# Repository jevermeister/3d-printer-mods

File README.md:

# 3d-printer-mods
my 3d printer mods which might or might not be useful

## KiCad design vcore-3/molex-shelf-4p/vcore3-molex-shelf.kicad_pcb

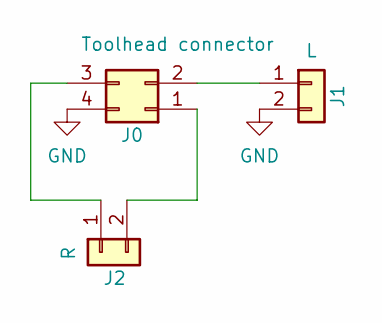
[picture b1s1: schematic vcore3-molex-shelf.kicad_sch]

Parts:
J0: Toolhead connector; Molex_Micro-Fit_3.0_43045-0412_2x02_P3.00mm_Vertical
J1: L; CONN-TH_2P-P5.08_796949-2
J2: R; CONN-TH_2P-P5.08_796949-2

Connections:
GND: J0.4, J1.2
unnamed: J0.1, J2.2
unnamed: J0.2, J1.1
unnamed: J0.3, J2.1

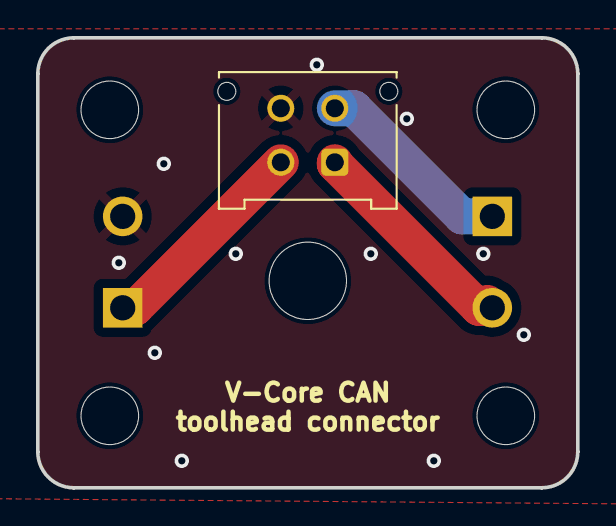
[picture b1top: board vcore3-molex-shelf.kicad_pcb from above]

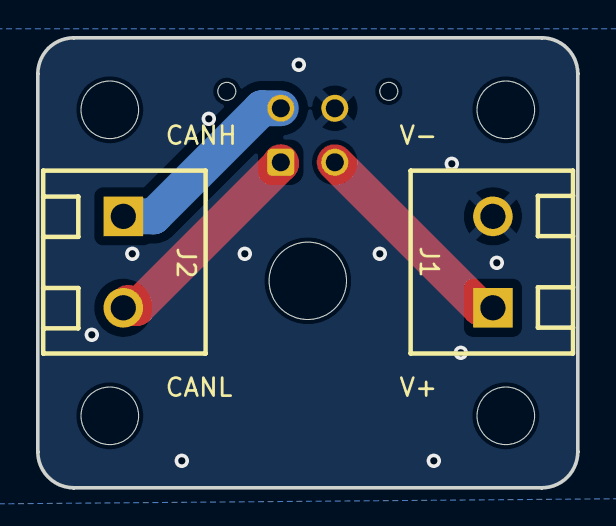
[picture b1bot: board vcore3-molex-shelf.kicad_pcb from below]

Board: 2 copper layers, 30.0 x 25.0 mm, 3 parts (2 on the bottom side), 4 nets.

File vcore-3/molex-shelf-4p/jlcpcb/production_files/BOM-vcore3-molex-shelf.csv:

Comment,Designator,Footprint,LCSC,Quantity
Toolhead connector,J0,Molex_Micro-Fit_3.0_43045-0412_2x02_P3.00mm_Vertical,,1
R,J2,CONN-TH_2P-P5.08_796949-2,,1
L,J1,CONN-TH_2P-P5.08_796949-2,,1

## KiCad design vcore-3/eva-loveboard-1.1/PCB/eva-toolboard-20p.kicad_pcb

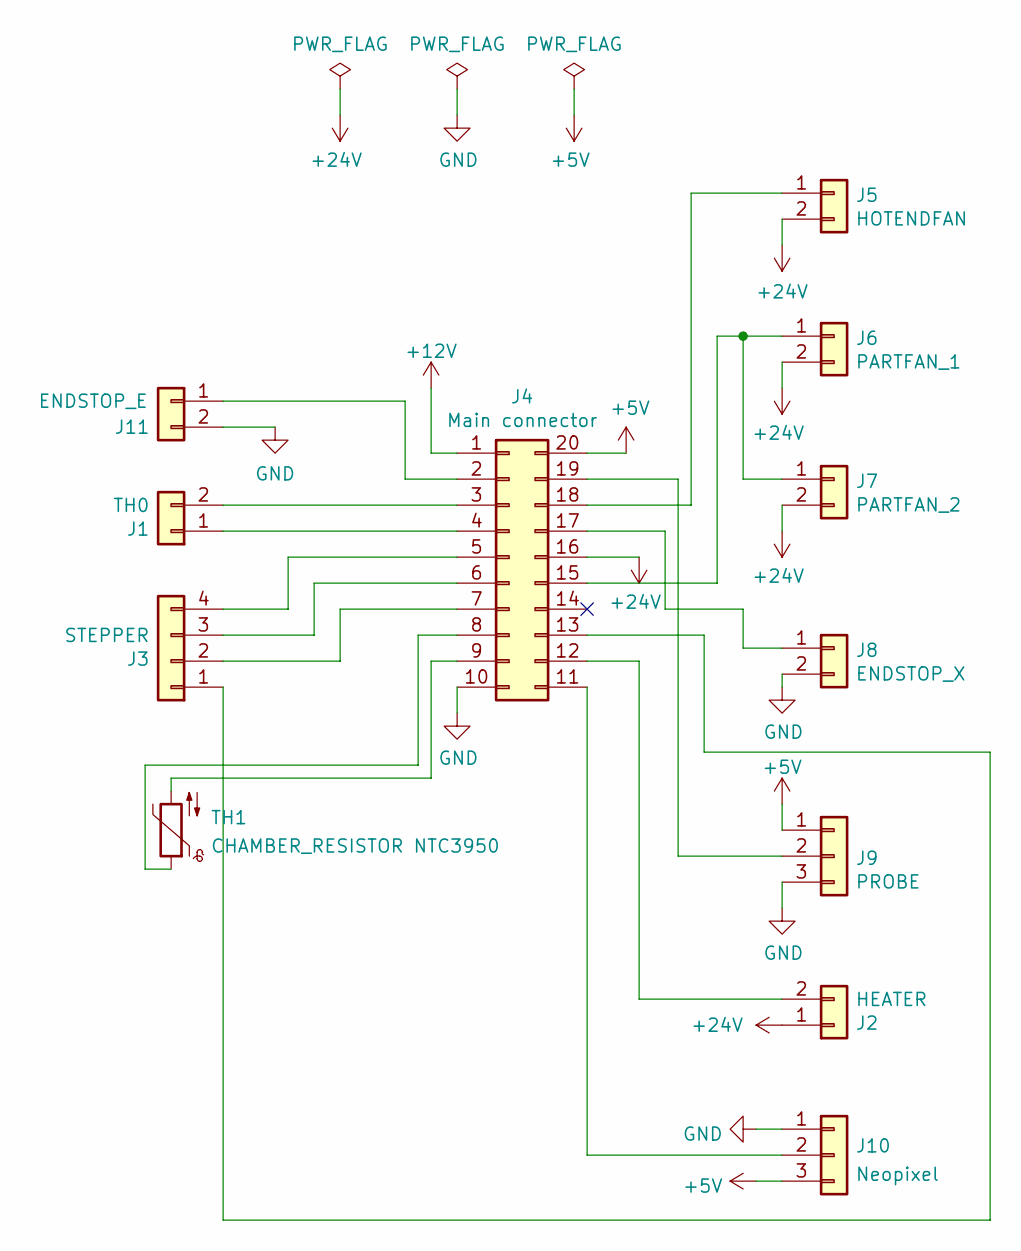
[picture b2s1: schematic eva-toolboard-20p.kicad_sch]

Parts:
J1: TH0; JST_PH_B2B-PH-K_1x02_P2.00mm_Vertical
J2: HEATER; Molex_Micro-Fit_3.0_43650-0200_1x02_P3.00mm_Horizontal
J3: STEPPER; JST_PH_B4B-PH-K_1x04_P2.00mm_Vertical
J4: Main connector; Molex_Micro-Fit_3.0_43045-2000_2x10_P3.00mm_Horizontal
J5: HOTENDFAN; JST_PH_S2B-PH-K_1x02_P2.00mm_Horizontal
J6: PARTFAN_1; JST_PH_S2B-PH-K_1x02_P2.00mm_Horizontal
J7: PARTFAN_2; JST_PH_B2B-PH-K_1x02_P2.00mm_Vertical
J8: ENDSTOP_X; JST_PH_S2B-PH-K_1x02_P2.00mm_Horizontal
J9: PROBE; JST_PH_S3B-PH-K_1x03_P2.00mm_Horizontal
J10: Neopixel; JST_PH_S3B-PH-K_1x03_P2.00mm_Horizontal
J11: ENDSTOP_E; JST_PH_B2B-PH-K_1x02_P2.00mm_Vertical
TH1: CHAMBER_RESISTOR NTC3950; D_A-405_P7.62mm_Horizontal

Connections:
+5V: J4.20, J9.1, J10.3
+12V: J4.1
+24V: J2.1, J4.16, J5.2, J6.2, J7.2
GND: J4.10, J8.2, J9.3, J10.1, J11.2
unnamed: J2.2, J4.12
unnamed: J3.1, J4.13
unnamed: J3.2, J4.7
unnamed: J3.3, J4.6
unnamed: J3.4, J4.5
unnamed: J4.2, J11.1
unnamed: J1.2, J4.3
unnamed: J1.1, J4.4
unnamed: J4.8, TH1.1
unnamed: J4.9, TH1.2
unnamed: J4.15, J6.1, J7.1
unnamed: J4.17, J8.1
unnamed: J4.18, J5.1
unnamed: J4.19, J9.2
unnamed: J4.11, J10.2

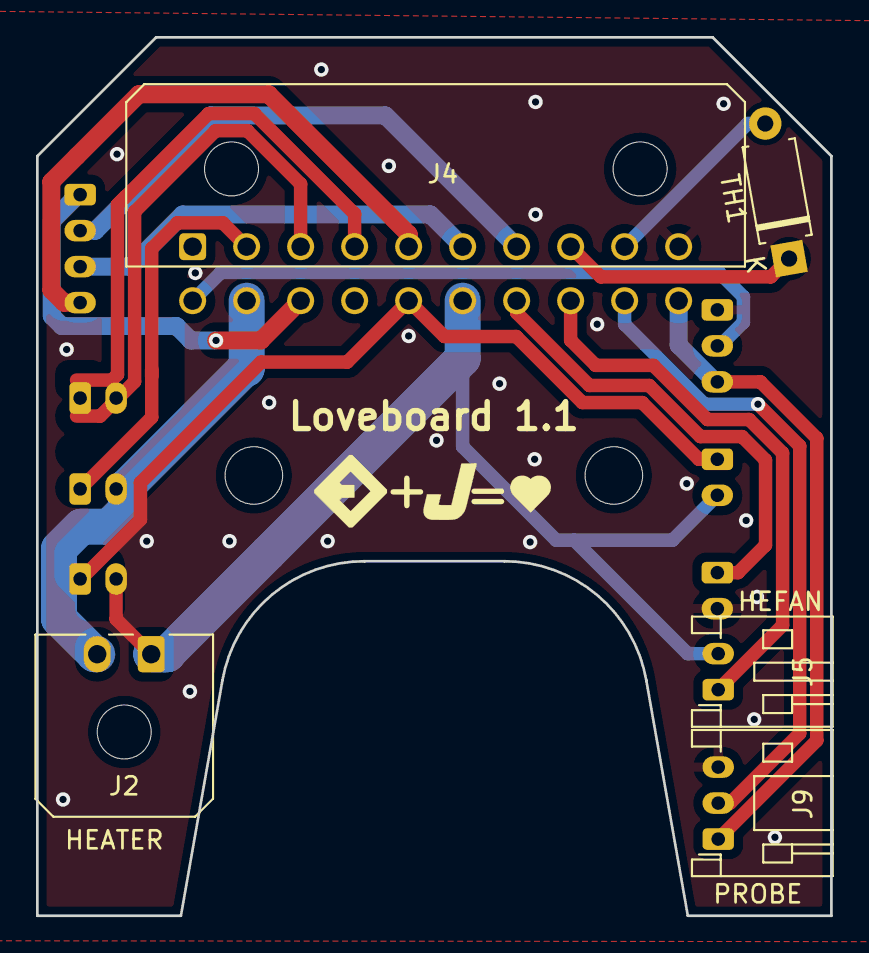
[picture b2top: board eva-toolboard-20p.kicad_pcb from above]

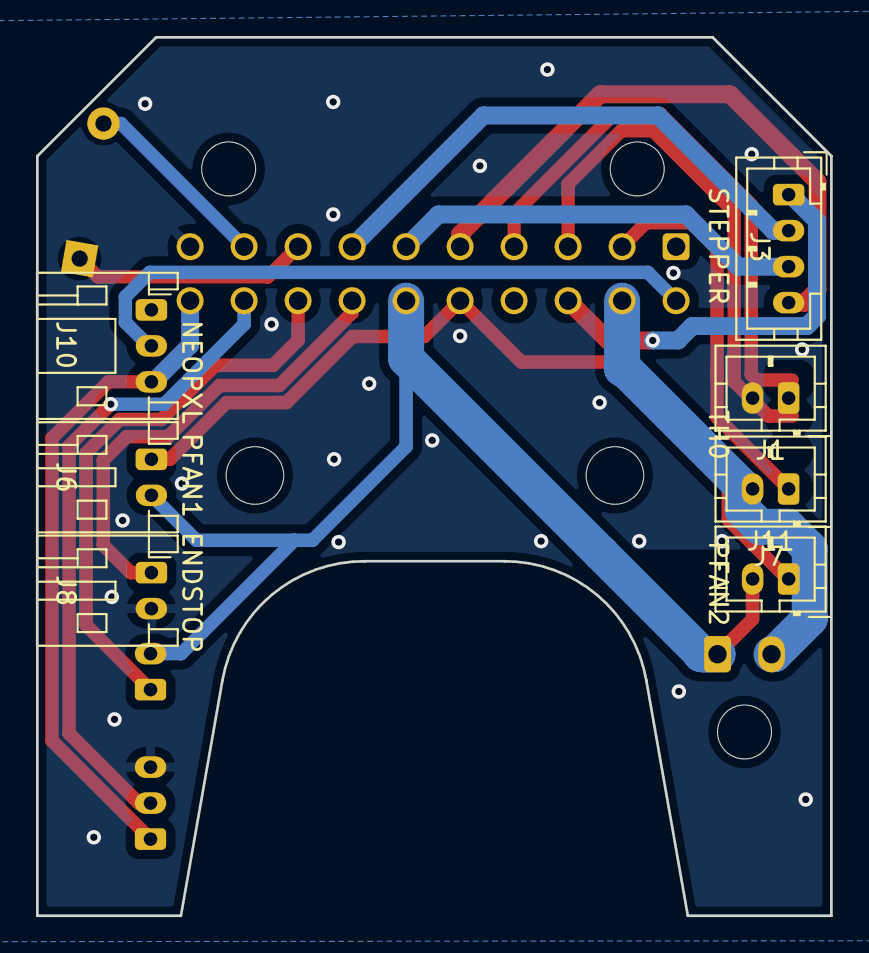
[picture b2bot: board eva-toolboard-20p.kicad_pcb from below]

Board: 2 copper layers, 44.1 x 48.8 mm, 17 parts (7 on the bottom side), 18 nets.

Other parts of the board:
L: MountingHole_3.2mm_M3
R: MountingHole_3.2mm_M3
svg2mod: G***; EVA_Logo
svg2mod#2: G***; Jevermeister_Logo
svg2mod#3: G***; Heart_Logo

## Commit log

2021-10-21 Added 3x5 wago 221-415 mount and readme
2021-10-21 Added pictures of the v0 221-415 wago mounts
2021-10-26 Added BTT Octopus tunnel
2021-10-26 Added license to readme
2021-10-26 Added license
2021-12-08 Added CAD snapshots
2021-12-08 Cropped pics
2021-12-09 Added BTT filament sensor backplate
2021-12-14 Added BTT Rumba32 mount and cooling tunnel
2021-12-14 Added din rail clamp notice
2021-12-14 Added reference to Walter Layhers design and renamed DIN mount to backplate
2021-12-24 Added V-Core 3 Voron-0.1 scaled handles
2021-12-24 Update README.md
    Corrected license part
2021-12-24 Removed non-compatible handles and made them a bit higher
2021-12-24 Update README.md
    Fixed typos and added Voron reference
2022-01-02 Updated images
2022-01-05 Moved V0 wago mods into separate directory
2022-01-05 Moved V-Core 3 stuff into separate directory
2022-01-06 Added V-Core 3 rear Z arm wago mount
2022-01-06 Corrected readme
2022-01-06 Added missing notes and items
2022-01-10 Added triple 221-412 wago holders
2022-01-10 Added Filadryer S1 PTFE fitting
2022-01-10 Added MPCNC squaring helper
2022-01-10 Added DC-DC din rail bracket
2022-01-10 Added GPLv3 into readme
2022-01-18 Initial dev board
2022-01-19 Routed PCB and adapted schematic
2022-01-20 Latest pcb update
2022-01-21 Added gerber settings for JLCPCB
2022-01-21 Added and moved connector labels
2022-01-21 Removed unconnected track ends
2022-01-21 Added totally useless but cute logos
2022-01-23 Beefed upper stepper tracks and some rerouting
2022-01-23 Added Neopixel and unified part fan V-
2022-01-23 Added via for a more consistent ground plane
2022-01-24 Added labels, corrected chamber thermistor
2022-01-24 Added a tiny GND area
2022-01-25 Corrected board outline clearance and added GND vias
2022-01-25 Moved via so it doesn't pierce the heart (ooh)
2022-01-25 and another via so it doesnt pierce the label
2022-01-30 Added gerber archive
2022-04-02 Added MPCNC z max endstop
2022-04-02 Renamed first board to avoid confusion
2022-04-02 Removed project file which is unnecessary
2022-04-02 Added initial commit of the generic loveboard with 2p thermistor
2022-04-02 First draft of the new 2p th board
2022-04-25 Added loveboard 4p CAD files
2022-04-29 Added pictures to illustrate the correct pins
2022-05-03 Corrected molex connector pins PNG
2025-03-01 added 4p molex shelf pcb
